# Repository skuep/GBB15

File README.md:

# GBB15
A gantry-mounted CAN stepper driver board for 15mm aluminum beams (mostly for PrintersForAnts printers). 

This board can be used e.g. for the Micron to have A/B motor controllers directly at the gantry. This reduces the number of wires required to be routed to the gantry.

Additionally, this board can be used for Voron-0 or Tridents as a USB to CAN converter (using the Klipper CAN bridge option) with **included** A/B motor controllers.

# JLCPCB Specifications
0. Upload ``GERBER-GBB15.zip``
1. Select Qty
2. PCB Thickness 1.6mm
3. LeadFree HASL
4. Enable PCB Assembly
5. Choose **Economic**
6. Select Assembly Side **Bottom Side**
7. Tooling holes: **Added by Customer**
8. Press **Confirm**
9. Upload ``BOM-GBB15.csv``and ``CPL-GBB15.csv``
10. Check that all parts are in stock and click **NEXT**
11. Look for odd placement in the preview, select **NEXT**

# Additionally needed LCSC parts
You can order these on LCSC

| Part                     | Quantity | Notes  | LCSC Part Number | Link  | 
| ------------------------ | :-: | ----------- | ----------- |----------- |
| 100u/35V/105°C capacitor | 2   |             | C3035369    | https://www.lcsc.com/product-detail/Aluminum-Electrolytic-Capacitors-Leaded_Rubycon-35YXJ100MFFCT1-6-3X11_C3035369.html |
| MicroFit 3.0 connector   | 2   | Tin or Gold | C277721 or C563821 | https://www.lcsc.com/product-detail/Wire-To-Board-Wire-To-Wire-Connector_MOLEX-430450412_C277721.html or https://www.lcsc.com/product-detail/Pre-ordered-Connectors_MOLEX-430450413_C563821.html |
| JST PH 2.0mm 2-Pin conn. | 4   | Endstop/Thermistors | C131337 | https://www.lcsc.com/product-detail/Wire-To-Board-Wire-To-Wire-Connector_JST-Sales-America-B2B-PH-K-S-LF-SN_C131337.html |
| JST XH 2.5mm 4-Pin conn. | 2   | Steppers    | C144395 | https://www.lcsc.com/product-detail/Wire-To-Board-Wire-To-Wire-Connector_JST-Sales-America-B4B-XH-A-LF-SN_C144395.html |
| Vertical THT USB-C conn. | 1   |             | C3151747 | https://www.lcsc.com/product-detail/USB-Connectors_SHOU-HAN-TYPE-C-16PLC-H10-0_C3151747.html |
| CAN termination resistor | 1   | Optional!   | C17909 | https://www.lcsc.com/product-detail/Chip-Resistor-Surface-Mount_UNI-ROYAL-Uniroyal-Elec-1206W4F1200T5E_C17909.html |
| Tactile Switches         | 2   | Boot/Reset  | C255802 | https://www.lcsc.com/product-detail/Tactile-Switches_HYP-Hongyuan-Precision-1TS002E-2500-2501-CT_C255802.html |
| Heat Sink                | 2   | Standard TMC2209 heatsink | C5250902 or C5250879 | https://www.lcsc.com/product-detail/Heat-sink-heatsink_wenhaoyongshun-D11-01-02_C5250902.html or https://www.lcsc.com/product-detail/Heat-sink-heatsink_wenhaoyongshun-F12-04-05_C5250879.html |
| 1.5mm M.2 Thermal pad    | 1   | Cut to size 67x15mm | -- | https://www.amazon.de/-/en/Assorted-Thickness-Conductive-Silicone-Conductivity/dp/B07X38254H (DE) or https://www.amazon.com/ADWITS-12-Pack-Conductive-Silicone-Conductivity/dp/B07X81PRK7 (US) |

# Quick Guide
1. Solder top components (order: 120R resistor (if required), switches, 4x JST PH 2.0mm, 2x JST XH2.5mm, 2x MicroFit 3.0 2x2, USB connector, Capacitors & attach heatsinks)
1. Attach 1.5mm heat gap filler pad to bottom, cut to size if required using a sharp knife
1. Poke screw holes into the gap filler pads
1. Use M3x8mm screws to attach to bottom of gantry frame (see above)

Note that thermal connection to the 15mm beam is required! Otherwise the Stepper motor controllers might overheat.

# Firmware
1.  Plug in USB cable and connect 24V power, the green LED on the bottom side (Rev. B and up) must light up.
    Hold BOOT pushbutton, while tapping the RESET pushbutton and release all buttons. This is the sequence to set the GBB15 into DFU mode.

    **IMPORTANT**: STMicro decided on the entire STM32G0 series to set the ``nBOOT_SEL`` option bit and thus disable the ``BOOT0`` pin by default.
    This means you would have only one shot at uploading a bootloader, while the flash is empty. If you choose to re-program the bootloader (e.g. other CAN speed), you cannot get into the DFU mode anymore.
    For enabling the "legacy" ``BOOT0`` pin functionality, you have two options.
    1. You can use STMicro's STM32CubeProgrammer software to disable the ``nBOOT_SEL`` option bit by following the screenshot [here](doc/BOOT0-Via-STM32CubeProgrammer.png).
    1. Or if you prefer ``dfu-util``, which is included (or easily installed) in major linux distros (e.g. Raspberry Pi OS), you can run the ``enable_boot.hex`` firmware from [here](https://github.com/olikraus/stm32g031/tree/main/enable_boot0). 
       It will clear the ``nBOOT_SEL`` option bit from within the firmware, if it is not yet cleared.
       Use the following commands to upload the file.
       ```` 
           objcopy --input-target=ihex --output-target=binary enable_boot0.hex enable_boot0.bin # Convert hex to binary
           sudo dfu-util -a 0 -d 0483:df11 --dfuse-address 0x08000000:leave -D enable_boot0.bin
       ````
       After waiting for a second, the ``BOOT0`` pin is now enabled again and you can continue normally. 

       **NOTE:** Before continuing, remember to set the GBB15 into DFU mode again using the BOOT/RESET pushbuttons (see above).

1.  Build CanBoot according the instructions on the [CanBoot](https://github.com/Arksine/katapult) github page. 
    See [this](doc/GBB15-CanBoot.png) image for CanBoot menuconfig settings to use.

1.  Build the Klipper firmware according to the instructions on the [Klipper](https://www.klipper3d.org/Installation.html#building-and-flashing-the-micro-controller) github page.
    See [this](doc/GBB15-klipper.png) image for Klipper menuconfig settings to use.

1.  Upload CanBoot to the GBB15 using either STM32CubeProgrammer (if you have it installed) or using ``dfu-util`` with these commands.
    ````
        sudo dfu-util -a 0 -d 0483:df11 --dfuse-address 0x08000000:leave -D out/canboot.bin
    ````
    The device is now booted into CanBoot mode and can be accessed using the CanBoot tools.

1.  Upload the Klipper firmware to the GBB15 using either CanBoot's ``flashtool.py`` as described [here](https://github.com/Arksine/katapult#uploading-klipper) or Klipper's ``make flash`` (uses ``dfu-util``).
    1.  Using ``flashtool.py`` via CAN. Run these commands from the ``CanBoot/scripts`` directory
        ````
            python3 flashtool.py -i can0 -q # Check the UUID of the GBB15 board
            python3 flashtool.py -i can0 -f ~/klipper/out/klipper.bin -u <uuid> # Insert UUID here
        ````
    1.  Using ``make flash`` via Klipper Makefile. Run this command from the ``klipper`` directory.

        **NOTE:** For this, you need to set the GBB15 into DFU mode again using the BOOT/RESET pushbuttons (see above).
        ````
            make flash FLASH_DEVICE=0483:df11
        ````

# Pinout
This image shows the pinout of the GBB15 PCB. The CAN connector layout is compatible to the BigTreeTech EBB36 board (among others).

# Klipper configuration
````
[mcu gantry_mcu]
canbus_interface: can0
canbus_uuid: f7b6d9f26b4a

...

[temperature_sensor chamber]
sensor_type: Generic 3950
sensor_pin: gantry_mcu:PA1 # SMD thermistor on GBB15 PCB
#sensor_pin: gantry_mcu:PA3 # Alternatively, this is STOP1 connector if it is not used otherwise
#sensor_pin: gantry_mcu:PA2 # Alternatively, this is STOP2 connector if it is not used otherwise (for Rev. B and up) 
pullup_resistor: 4700

[temperature_sensor Motor_A]
sensor_type: Generic 3950
sensor_pin: gantry_mcu:PB11 # TH_A on GBB15 PCB
pullup_resistor: 4700

[temperature_sensor Motor_B]
sensor_type: Generic 3950
sensor_pin: gantry_mcu:PB12 # TH_B on GBB15 PCB
pullup_resistor: 4700

[temperature_sensor gantry_temp]
sensor_type: temperature_mcu
sensor_mcu: gantry_mcu
min_temp: 0
max_temp: 100

...

[stepper_y]
step_pin: gantry_mcu:PB2
dir_pin: gantry_mcu:PB1
enable_pin: !gantry_mcu:PB13
endstop_pin: gantry_mcu:PA3 # This is the STOP1 connector on GBB15 PCB
#endstop_pin: gantry_mcu:PA2 # Alternatively, this is STOP2 connector (for Rev. B and up, PC13 on Rev. A)
...

[tmc2209 stepper_y]
uart_pin: gantry_mcu:PA4
sense_resistor: 0.110
diag_pin: gantry_mcu:PB0
...

[stepper_x]
step_pin: gantry_mcu:PB7
dir_pin: gantry_mcu:PB8
enable_pin: !gantry_mcu:PB9
endstop_pin: gantry_mcu:PA2 # This is STOP2 connector (for Rev. B and up, PC13 on Rev. A)
#endstop_pin: gantry_mcu:PA3 # Alternatively, this is the STOP1 connector on GBB15 PCB
...

[tmc2209 stepper_x]
uart_pin: gantry_mcu:PB3
sense_resistor: 0.110
diag_pin: PB5
...

````

"Chamber" thermistor in this configuration is a SMD thermistor on the PCB. It reads probably 15-20°C above the actual chamber temperature, when the stepper motors are enabled and running. 
- To get better chamber temp readings, you can use TH_A or TH_B to connect a remote thermistor (in case you don't need those for monitoring the motor temperatures). 
- Alternatively you can (mis-)use the STOP1 (All revisions) and STOP2 (Rev. B and up) pins for analog readings. Easiest is a through-hole 100K B3950 NTC crimped into a JST PH2.0 and connected to one of the mentioned header pins.

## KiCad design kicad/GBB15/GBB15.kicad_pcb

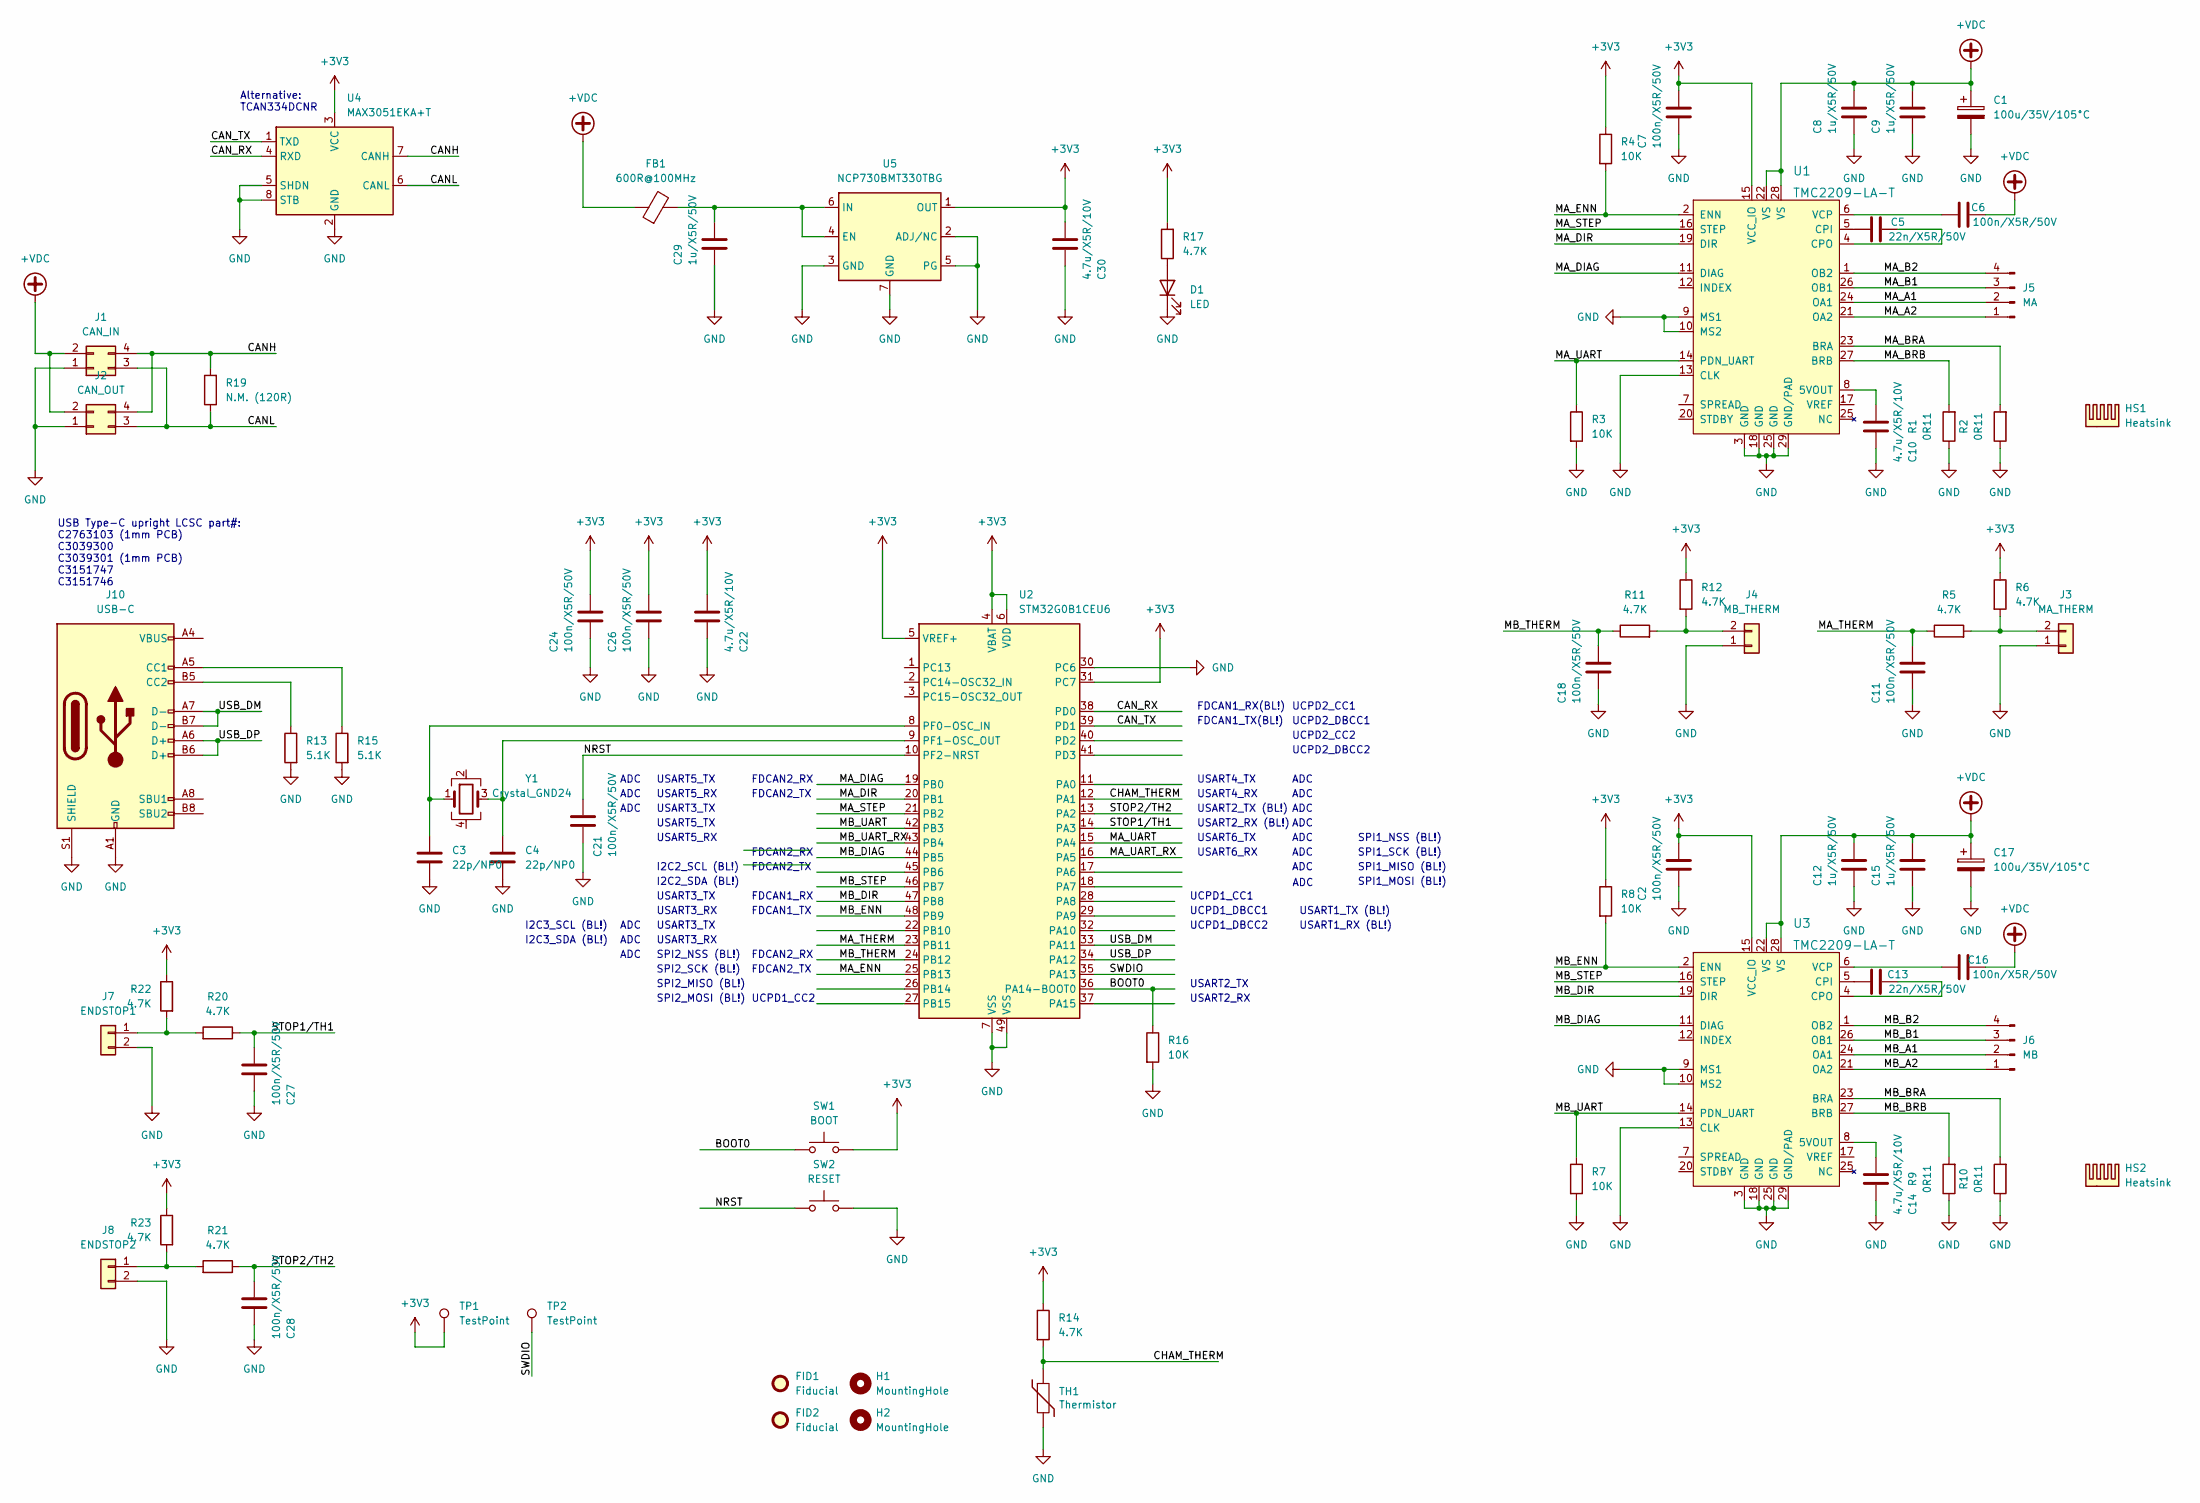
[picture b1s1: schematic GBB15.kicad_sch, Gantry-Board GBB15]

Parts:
C1, C17: 100u/35V/105°C; CP_Radial_D6.3mm_P2.50mm; LCSC C3035369
C2, C6, C7, C11, C16, C18, C21, C24, C26, C27, C28: 100n/X5R/50V; C_0603_1608Metric; LCSC C14663
C3, C4: 22p/NP0; C_0603_1608Metric; LCSC C1653
C5, C13: 22n/X5R/50V; C_0603_1608Metric; LCSC C21122
C8, C9, C12, C15, C29: 1u/X5R/50V; C_0805_2012Metric; LCSC C28323
C10, C14, C22, C30: 4.7u/X5R/10V; C_0603_1608Metric; LCSC C19666
D1: LED; LED_0603_1608Metric; LCSC C72043
FB1: 600R@100MHz; L_0603_1608Metric; LCSC C1002
FID1, FID2: Fiducial; TOOLING-HOLE
H1, H2: MountingHole; MountingHole_3.2mm_M3
HS1, HS2: Heatsink; TMC2209-Heatsink
J1: CAN_IN; Molex_Micro-Fit_3.0_43045-0412_2x02_P3.00mm_Vertical; LCSC C563821
J2: CAN_OUT; Molex_Micro-Fit_3.0_43045-0412_2x02_P3.00mm_Vertical; LCSC C563821
J3: MA_THERM; JST_PH_B2B-PH-K_1x02_P2.00mm_Vertical; LCSC C131337
J4: MB_THERM; JST_PH_B2B-PH-K_1x02_P2.00mm_Vertical; LCSC C131337
J5: MA; JST_XH_B4B-XH-A_1x04_P2.50mm_Vertical; LCSC C144395
J6: MB; JST_XH_B4B-XH-A_1x04_P2.50mm_Vertical; LCSC C144395
J7: ENDSTOP1; JST_PH_B2B-PH-K_1x02_P2.00mm_Vertical; LCSC C131337
J8: ENDSTOP2; JST_PH_B2B-PH-K_1x02_P2.00mm_Vertical; LCSC C131337
J10: USB-C; TYPE-C 16PLC-H10.0; LCSC C3151747
R1, R2, R9, R10: 0R11; R_1206_3216Metric; LCSC C2934288
R3, R4, R7, R8, R16: 10K; R_0603_1608Metric; LCSC C25804
R5, R6, R11, R12, R14, R17, R20, R21, R22, R23: 4.7K; R_0603_1608Metric; LCSC C23162
R13, R15: 5.1K; R_0603_1608Metric; LCSC C23186
R19: N.M. (120R); R_1206_3216Metric; LCSC C17909
SW1: BOOT; SW_SPST_CK_RS282G05A3; LCSC C255802
SW2: RESET; SW_SPST_CK_RS282G05A3; LCSC C255802
TH1: Thermistor; R_0603_1608Metric; LCSC C919169
TP1, TP2: TestPoint; TestPoint_Pad_1.5x1.5mm
U1, U3: TMC2209-LA-T; QFN-28-1EP_5x5mm_P0.5mm_EP3.35x3.35mm; MPN TMC2209-LA-T; Digi-Key_PN 1460-1398-2-ND
U2: STM32G0B1CEU6; QFN-48-1EP_7x7mm_P0.5mm_EP5.6x5.6mm; LCSC C2829190
U4: MAX3051EKA+T; SOT-23-8; LCSC C112005
U5: NCP730BMT330TBG; DFN-6-1EP_2x2mm_P0.65mm_EP1x1.6mm; LCSC C892821
Y1: Crystal_GND24; Crystal_SMD_3225-4Pin_3.2x2.5mm; LCSC C2682774

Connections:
+3V3: C2.2, C7.2, C22.2, C24.2, C26.2, C30.2, R4.1, R6.1, R8.1, R12.1, R14.1, R17.2, R22.1, R23.1, SW1.2, TP1.1, U1.15 (VCC_IO), U2.4 (VBAT), U2.5 (VREF+), U2.6 (VDD), U2.31 (PC7), U3.15 (VCC_IO), U4.3 (VCC), U5.1 (OUT)
+VDC: C1.1, C6.2, C8.2, C9.2, C12.2, C15.2, C16.2, C17.1, FB1.1, J1.2, J2.2, U1.22 (VS), U1.28 (VS), U3.22 (VS), U3.28 (VS)
/BOOT0: R16.1, SW1.1, U2.36 (PA14-BOOT0)
/CANH: J1.4, J2.4, R19.2, U4.7 (CANH)
/CANL: J1.3, J2.3, R19.1, U4.6 (CANL)
/CAN_RX: U2.38 (PD0), U4.4 (RXD)
/CAN_TX: U2.39 (PD1), U4.1 (TXD)
/CHAM_THERM: R14.2, TH1.1, U2.12 (PA1)
/MA_A1: J5.2, U1.24 (OA1)
/MA_A2: J5.1, U1.21 (OA2)
/MA_B1: J5.3, U1.26 (OB1)
/MA_B2: J5.4, U1.1 (OB2)
/MA_BRA: R2.2, U1.23 (BRA)
/MA_BRB: R1.2, U1.27 (BRB)
/MA_DIAG: U1.11 (DIAG), U2.19 (PB0)
/MA_DIR: U1.19 (DIR), U2.20 (PB1)
/MA_ENN: R4.2, U1.2 (ENN), U2.25 (PB13)
/MA_STEP: U1.16 (STEP), U2.21 (PB2)
/MA_THERM: C11.2, R5.1, U2.23 (PB11)
/MA_UART: R3.1, U1.14 (PDN_UART), U2.15 (PA4)
/MA_UART_RX: U2.16 (PA5)
/MB_A1: J6.2, U3.24 (OA1)
/MB_A2: J6.1, U3.21 (OA2)
/MB_B1: J6.3, U3.26 (OB1)
/MB_B2: J6.4, U3.1 (OB2)
/MB_BRA: R10.2, U3.23 (BRA)
/MB_BRB: R9.2, U3.27 (BRB)
/MB_DIAG: U2.44 (PB5), U3.11 (DIAG)
/MB_DIR: U2.47 (PB8), U3.19 (DIR)
/MB_ENN: R8.2, U2.48 (PB9), U3.2 (ENN)
/MB_STEP: U2.46 (PB7), U3.16 (STEP)
/MB_THERM: C18.2, R11.1, U2.24 (PB12)
/MB_UART: R7.1, U2.42 (PB3), U3.14 (PDN_UART)
/MB_UART_RX: U2.43 (PB4)
/NRST: C21.2, SW2.1, U2.10 (PF2-NRST)
/STOP1/TH1: C27.2, R20.1, U2.14 (PA3)
/STOP2/TH2: C28.2, R21.1, U2.13 (PA2)
/SWDIO: TP2.1, U2.35 (PA13)
/USB_DM: J10.A7 (D-), J10.B7 (D-), U2.33 (PA11)
/USB_DP: J10.A6 (D+), J10.B6 (D+), U2.34 (PA12)
GND: C1.2, C2.1, C3.1, C4.1, C7.1, C8.1, C9.1, C10.1, C11.1, C12.1, C14.1, C15.1, C17.2, C18.1, C21.1, C22.1, C24.1, C26.1, C27.1, C28.1, C29.1, C30.1, D1.1 (K), J1.1, J2.1, J3.1, J4.1, J7.2, J8.2, J10.A1 (GND), J10.A12 (GND), J10.B1 (GND), J10.B12 (GND), J10.S1 (SHIELD), R1.1, R2.1, R3.2, R7.2, R9.1, R10.1, R13.2, R15.2, R16.2, SW2.2, TH1.2, U1.3 (GND), U1.9 (MS1), U1.10 (MS2), U1.13 (CLK), U1.18 (GND), U1.25 (GND), U1.29 (GND/PAD), U2.7 (VSS), U2.30 (PC6), U2.49 (VSS), U3.3 (GND), U3.9 (MS1), U3.10 (MS2), U3.13 (CLK), U3.18 (GND), U3.25 (GND), U3.29 (GND/PAD), U4.2 (GND), U4.5 (SHDN), U4.8 (STB), U5.2 (ADJ/NC), U5.3 (GND), U5.5 (PG), U5.7 (GND)
unnamed: C3.2, U2.8 (PF0-OSC_IN), Y1.1
unnamed: C4.2, U2.9 (PF1-OSC_OUT), Y1.3
unnamed: C5.1, U1.4 (CPO)
unnamed: C5.2, U1.5 (CPI)
unnamed: C6.1, U1.6 (VCP)
unnamed: C10.2, U1.8 (5VOUT)
unnamed: C13.1, U3.4 (CPO)
unnamed: C13.2, U3.5 (CPI)
unnamed: C14.2, U3.8 (5VOUT)
unnamed: C16.1, U3.6 (VCP)
unnamed: C29.2, FB1.2, U5.4 (EN), U5.6 (IN)
unnamed: D1.2 (A), R17.1
unnamed: J3.2, R5.2, R6.2
unnamed: J4.2, R11.2, R12.2
unnamed: J7.1, R20.2, R22.2
unnamed: J8.1, R21.2, R23.2
unnamed: J10.A4 (VBUS), J10.A9 (VBUS), J10.B4 (VBUS), J10.B9 (VBUS)
unnamed: J10.A5 (CC1), R15.1
unnamed: J10.B5 (CC2), R13.1

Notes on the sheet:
SPI2_MOSI (BL!)
USART5_RX
ADC
USART4_RX
UCPD2_DBCC1
Alternative: TCAN334DCNR
FDCAN2_RX
UCPD1_CC2
USART3_TX
USART4_TX
FDCAN2_TX
FDCAN1_RX
UCPD1_CC1
SPI1_SCK (BL!)
SPI2_MISO (BL!)
USART1_TX (BL!)
USART2_TX
I2C3_SDA (BL!)
USART2_TX (BL!)
USART5_TX
I2C3_SCL (BL!)
SPI1_MOSI (BL!)
SPI2_SCK (BL!)
FDCAN1_TX(BL!)
USART2_RX
USART3_RX
I2C2_SCL (BL!)
FDCAN1_RX(BL!)
FDCAN1_TX
USART2_RX (BL!)
USART1_RX (BL!)
SPI2_NSS (BL!)
USB Type-C upright LCSC part#: C2763103 (1mm PCB) C3039300 C3039301 (1mm PCB) C3151747 C3151746
USART6_RX
UCPD1_DBCC1
I2C2_SDA (BL!)
SPI1_NSS (BL!)
UCPD2_CC2
SPI1_MISO (BL!)
UCPD2_CC1

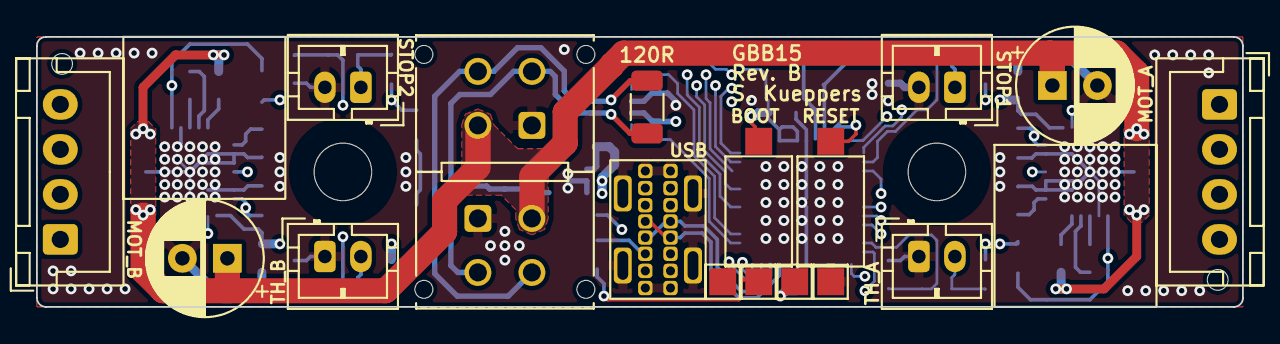
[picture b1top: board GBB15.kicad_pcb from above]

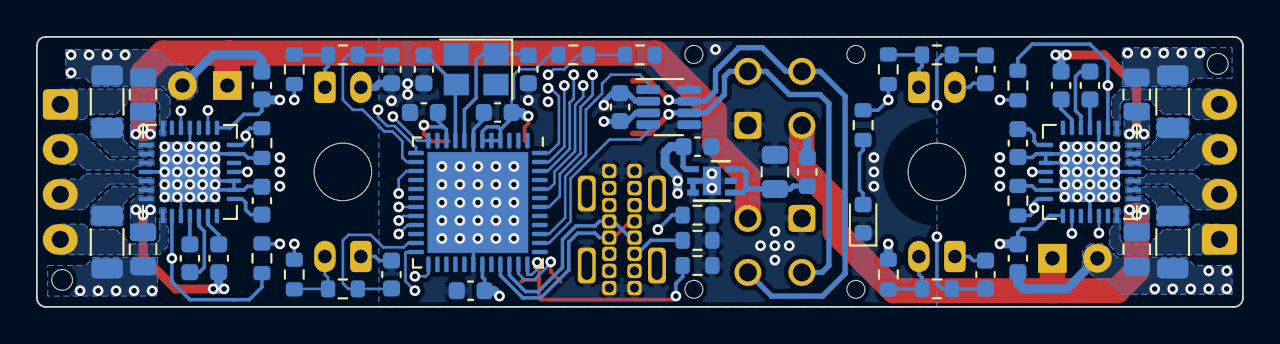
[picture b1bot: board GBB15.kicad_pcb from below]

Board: 4 copper layers, 67.0 x 15.0 mm, 76 parts (54 on the bottom side), 58 nets.

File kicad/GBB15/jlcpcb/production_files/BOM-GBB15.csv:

Comment,Designator,Footprint,LCSC
600R@100MHz,FB1,L_0603_1608Metric,C1002
MAX3051EKA+T,U4,SOT-23-8,C112005
MA_THERM,"J3,J4,J7,J8",JST_PH_B2B-PH-K_1x02_P2.00mm_Vertical,C131337
MA,"J5,J6",JST_XH_B4B-XH-A_1x04_P2.50mm_Vertical,C144395
100n/X5R/50V,"C11,C16,C18,C2,C21,C24,C26,C27,C28,C6,C7",C_0603_1608Metric,C14663
22p/NP0,"C3,C4",C_0603_1608Metric,C1653
N.M. (120R),R19,R_1206_3216Metric,C17909
4.7u/X5R/10V,"C10,C14,C22,C30",C_0603_1608Metric,C19666
22n/X5R/50V,"C13,C5",C_0603_1608Metric,C21122
4.7K,"R11,R12,R14,R17,R20,R21,R22,R23,R5,R6",R_0603_1608Metric,C23162
5.1K,"R13,R15",R_0603_1608Metric,C23186
BOOT,"SW1,SW2",SW_SPST_CK_RS282G05A3,C255802
10K,"R16,R3,R4,R7,R8",R_0603_1608Metric,C25804
Crystal_GND24,Y1,Crystal_SMD_3225-4Pin_3.2x2.5mm,C2682774
STM32G0B1CEU6,U2,QFN-48-1EP_7x7mm_P0.5mm_EP5.6x5.6mm,C2829190
1u/X5R/50V,"C12,C15,C29,C8,C9",C_0805_2012Metric,C28323
0R11,"R1,R10,R2,R9",R_1206_3216Metric,C2934288
100u/35V/105°C,"C1,C17",CP_Radial_D6.3mm_P2.50mm,C3035369
USB-C,J10,TYPE-C 16PLC-H10.0,C3151747
TMC2209-LA-T,"U1,U3",QFN-28-1EP_5x5mm_P0.5mm_EP3.35x3.35mm,C465949
CAN_IN,"J1,J2",Molex_Micro-Fit_3.0_43045-0412_2x02_P3.00mm_Vertical,C563821
LED,D1,LED_0603_1608Metric,C72043
NCP730BMT330TBG,U5,DFN-6-1EP_2x2mm_P0.65mm_EP1x1.6mm,C892821
Thermistor,TH1,R_0603_1608Metric,C919169
MountingHole,H2,MountingHole_3.2mm_M3,
MountingHole,H1,MountingHole_3.2mm_M3,
Heatsink,HS2,TMC2209-Heatsink,
Heatsink,HS1,TMC2209-Heatsink,
Fiducial,FID1,TOOLING-HOLE,
Fiducial,FID2,TOOLING-HOLE,
TestPoint,TP2,TestPoint_Pad_1.5x1.5mm,
TestPoint,TP1,TestPoint_Pad_1.5x1.5mm,

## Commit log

2023-06-06 Work in progress, layout close to finish
2023-06-06 Corrected USB footprint, renamed some signals
2023-06-06 Renamed project to GBB15
2023-06-06 Minor touches
2023-06-06 Removed unnecessary files
2023-06-06 PCB cleanup
2023-06-07 Small changes in JST connector type
2023-06-07 Added JLCPCB database and selected parts from LCSC
2023-06-07 Added LCSC properties in schematic
2023-06-07 Connected unconnected pads on TCAN334 to ground
2023-06-07 Added JLCPCB production files
2023-06-07 Correct 100nF capacitor part number and changed to MAX3051 instead of TCAN334
2023-06-07 Added tooling holes
2023-06-07 Corrected rotations for ICs
2023-06-07 Added rotation overrides file
2023-06-07 Added 3D STEP file
2023-06-07 Added PCB images
2023-06-07 Added README
2023-06-07 Added thermal pad
2023-06-08 Changed silkscreen
2023-06-08 Added image of GBB15 mounted on Micron gantry
2023-06-25 Update README.md
    Added Klipper stuff
2023-06-27 Bumped revision to B, added Power LED and moved ENDSTOP2 to ADC pin
2023-06-29 Added photograph
2023-07-16 Added pinout documentation on User.Drawings layer
2023-07-16 Added additional debug pads for SWD
2023-07-16 Updated production files
2023-07-16 Increased connection width to MicroFit GND pads
2023-07-16 Updated 3D data
2023-07-16 Added schematics and canboot/klipper configs
2023-07-16 Added pinout image
2023-07-16 Added more information to README
2023-07-16 Modified order of pinout image
2023-07-23 Minor trace changes
2023-08-06 Added much more information to README.md
2023-08-06 Minor changes to README.md
